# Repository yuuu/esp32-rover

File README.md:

# esp32-rover

A small, low-cost differential-drive rover for experimenting with SLAM. A Seeed XIAO ESP32-S3 drives two geared DC motors with encoders, and a YDLIDAR X2 2D LiDAR sits on top. The frame is 3D-printed and generated from a parametric FreeCAD script.

Inspired by the Vstone LightRover E32 and the Maker's Pet Mini.

> **Status:** early prototype. The rover drives a 50 cm square using wheel odometry only (in C and in Ruby). A Wi-Fi bridge and a host-side SLAM are written and tested in simulation; they have not run with the LiDAR yet.

## Hardware
| Part | Model |
|---|---|
| MCU | Seeed Studio XIAO ESP32-S3 |
| Motor driver | Toshiba TC78H653FTG (IN/IN mode) |
| Motors | MERCURY MG12A06E-060310-50 (6 V, 1:50, 7 PPR encoder) ×2 |
| Tires | FEETECH FS90R-W rubber tires (Φ60) on printed wheels |
| LiDAR | YDLIDAR X2 |
| Battery | 6× AA in a COMF BH-363-1B holder |
| Caster | Φ11.7 mm ball in a printed holder ×2 |

The motor supply (VM) comes from a 5 V L7805 regulator. Do not connect the battery directly to VM, because the TC78H653 is rated for at most 7.5 V.

The frame has three Φ130 mm decks:
- **Base:** motors, battery and casters
- **Mid deck:** main board
- **Top deck:** LiDAR

The overall height is about 141 mm.

## Repository layout
```
cad/
  frame.py        Parametric frame (FreeCAD Python). Single source for the model and STLs
  frame.FCStd     Generated assembly model
  test_fit.py     Generates small test-fit pieces
  stl/            Printable parts (Base_Plate, Mid_Deck, Top_Deck, Wheel_x2, Caster_x2)
  stl/test/       Test-fit pieces (generated, not tracked)
pcb/              Main board (KiCad): 60×60 mm, M3 holes on a 50 mm pitch
firmware/         Firmware projects, one directory each (see firmware/README.md)
  components/rover/  Rover hardware shared by the C projects (rover_config.h: pins, dimensions, gains)
  c-square/       C (ESP-IDF): drives a square by wheel odometry
  ruby-square/    Ruby (espinel): the same square run
  c-slam-bridge/  C (ESP-IDF): Wi-Fi bridge that streams odometry and LiDAR data to a SLAM host
host/
  ruby-slam/      Host-side SLAM in plain Ruby, with a simulator to try it without the hardware
```

## Building the frame
Requires FreeCAD (`freecadcmd`).

```sh
freecadcmd cad/frame.py      # writes cad/frame.FCStd and cad/stl/*.stl
freecadcmd cad/test_fit.py   # writes cad/stl/test/*.stl
```

All dimensions are constants at the top of `cad/frame.py`. The base bottom is flat, so it prints without supports. The wheels need supports for the outer rim.

## Firmware
Each directory under `firmware/` is a project of its own, named `<language>-<purpose>`. See [firmware/README.md](firmware/README.md) for the list and how to build each one.

| Project | |
|---|---|
| [`c-square`](firmware/c-square/) | Drives a 50 cm square by wheel odometry (feedforward + PI wheel speed control at 100 Hz, trapezoidal profiles) |
| [`ruby-square`](firmware/ruby-square/) | The same square run written in Ruby, compiled ahead of time by [espinel](https://github.com/yuuu/espinel) |
| [`c-slam-bridge`](firmware/c-slam-bridge/) | Joins Wi-Fi, streams odometry and the raw LiDAR bytes over UDP, and drives at the velocity the host commands |

> ⚠️ `c-square` and `ruby-square` start driving right after reset, including right after flashing. USB power alone can spin the motors, so lift the rover before flashing.

## SLAM (host side)
[`host/ruby-slam`](host/ruby-slam/) is a small scan-matching SLAM in plain Ruby (no gems). It talks to `c-slam-bridge`, and it comes with a simulated rover and room, so the whole pipeline can be tried before the LiDAR is mounted:

```sh
cd host/ruby-slam
bin/simulate                         # offline: writes out/map.png and compares SLAM with the ground truth
bin/fake_rover &                     # a stand-in for the rover on UDP
bin/slam_bridge 127.0.0.1 --auto     # the same program you point at the real rover
```

## Roadmap
- Run `c-slam-bridge` and `host/ruby-slam` with the LiDAR mounted; check the X2's angle offset
- Loop closure for the SLAM
- Tune the wheel speed controller
- Add a power switch, and replace the L7805 with a switching regulator

## License
MIT. See [LICENSE](LICENSE). This covers the firmware, the CAD scripts and generated models, and the KiCad board files.

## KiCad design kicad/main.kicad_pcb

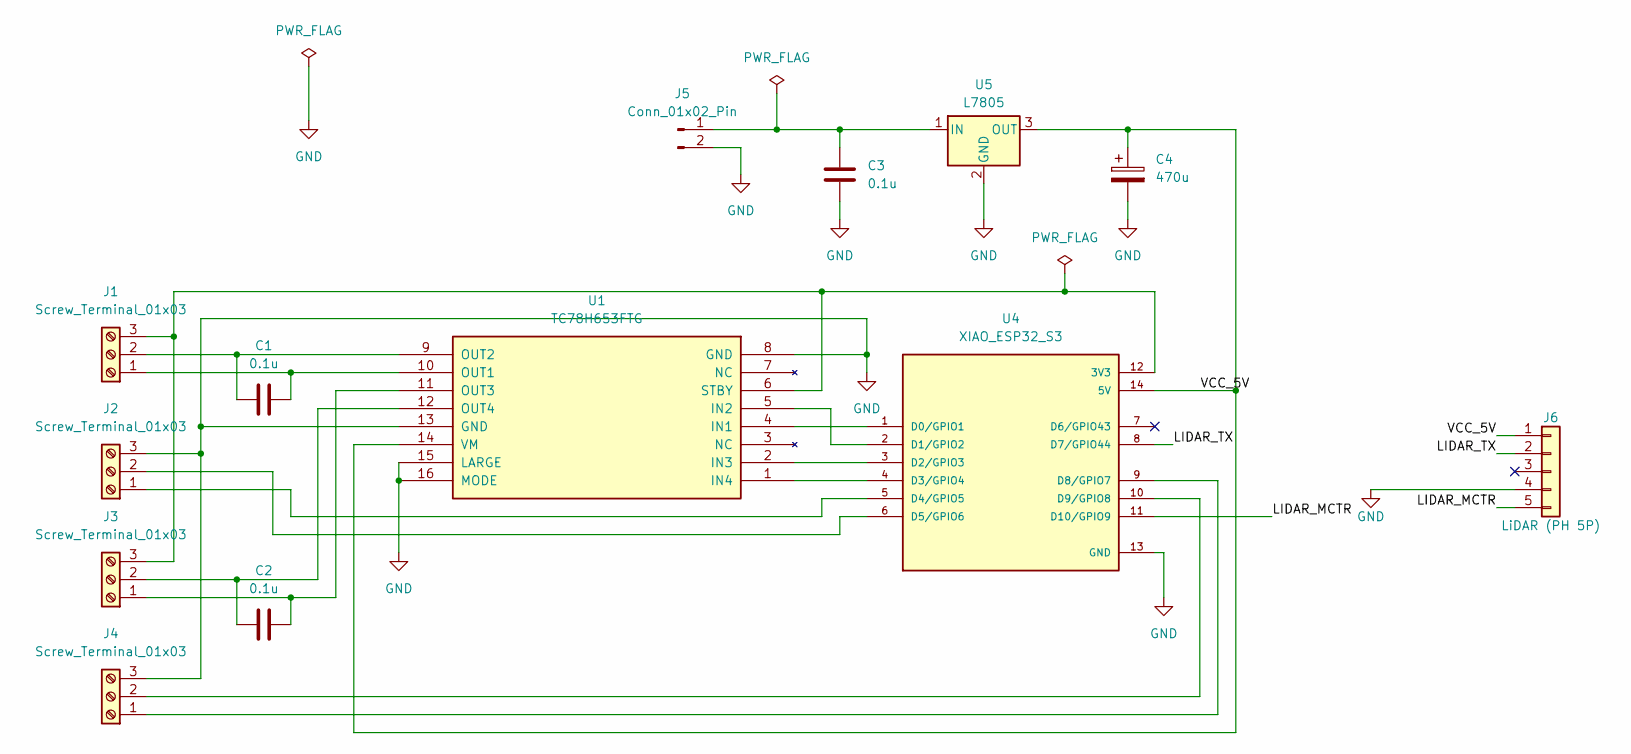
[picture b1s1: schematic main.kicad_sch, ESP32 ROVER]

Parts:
C1, C2, C3: 0.1u; C_Disc_D4.3mm_W1.9mm_P5.00mm
C4: 470u; CP_Radial_D8.0mm_P3.50mm
J1, J2, J3, J4: Screw_Terminal_01x03; TerminalBlock_CUI_TB007-508-03_1x03_P5.08mm_Horizontal
J5: Conn_01x02_Pin; PinHeader_1x02_P2.54mm_Vertical
J6: LiDAR (PH 5P); JST_PH_B5B-PH-K_1x05_P2.00mm_Vertical; MPN B5B-PH-K-S(LF)(SN)
U1: TC78H653FTG; AE-TC78H653FTG
U4: XIAO_ESP32_S3; MODULE_XIAO_ESP32_S3; PARTREV April 22nd, 2026
U5: L7805; TO254P1030X480X2260-3

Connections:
/LIDAR_MCTR: J6.5, U4.11 (D10/GPIO9)
/LIDAR_TX: J6.2, U4.8 (D7/GPIO44)
/VCC_5V: C4.1, J6.1, U1.14 (VM), U4.14 (5V), U5.3 (OUT)
GND: C3.2, C4.2, J2.3, J4.3, J5.2, J6.4, U1.8 (GND), U1.13 (GND), U1.15 (LARGE), U1.16 (MODE), U4.13 (GND), U5.2 (GND)
unnamed: C1.1, J1.1, U1.10 (OUT1)
unnamed: C1.2, J1.2, U1.9 (OUT2)
unnamed: J1.3, J3.3, U1.6 (STBY), U4.12 (3V3)
unnamed: J2.1, U4.5 (D4/GPIO5)
unnamed: J2.2, U4.6 (D5/GPIO6)
unnamed: C2.2, J3.1, U1.11 (OUT3)
unnamed: C2.1, J3.2, U1.12 (OUT4)
unnamed: J4.1, U4.9 (D8/GPIO7)
unnamed: J4.2, U4.10 (D9/GPIO8)
unnamed: C3.1, J5.1, U5.1 (IN)
unnamed: U1.4 (IN1), U4.1 (D0/GPIO1)
unnamed: U1.5 (IN2), U4.2 (D1/GPIO2)
unnamed: U1.2 (IN3), U4.3 (D2/GPIO3)
unnamed: U1.1 (IN4), U4.4 (D3/GPIO4)

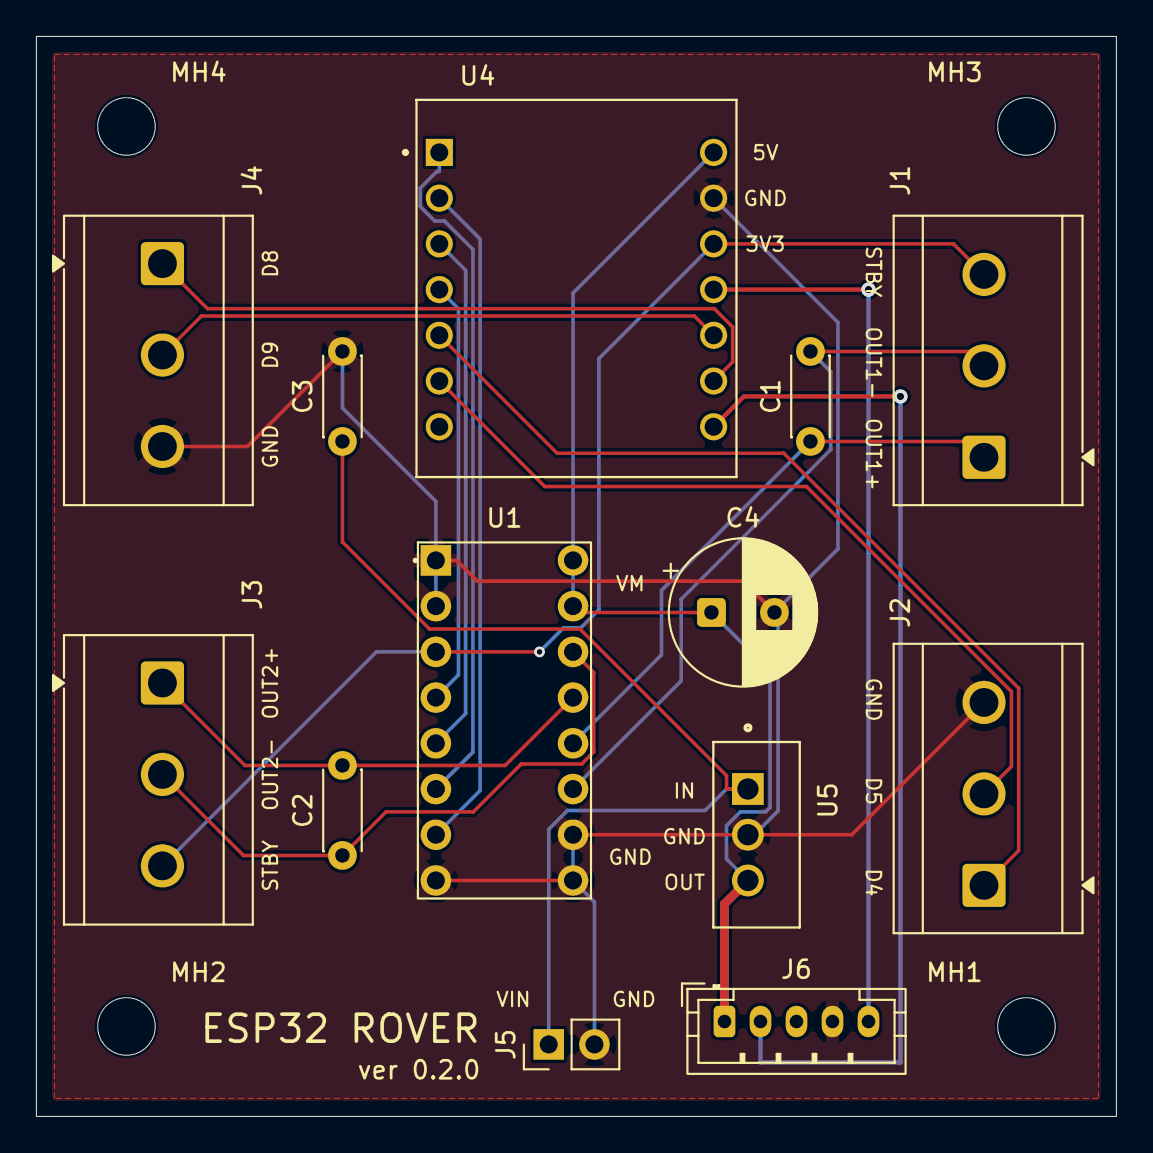
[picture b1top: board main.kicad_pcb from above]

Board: 2 copper layers, 60.0 x 60.0 mm, 17 parts (0 on the bottom side), 18 nets.

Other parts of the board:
MH1, MH2, MH3, MH4: MountingHole_3.2mm_M3
